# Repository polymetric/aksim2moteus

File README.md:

# aksim2moteus

RS422 adapter with a pinout specifically to adapt a moteus to an aksim2 

screw pattern is M2 - 10.2 x 12.7 mm

overall board dimensions 25.4 x 17.8 mm

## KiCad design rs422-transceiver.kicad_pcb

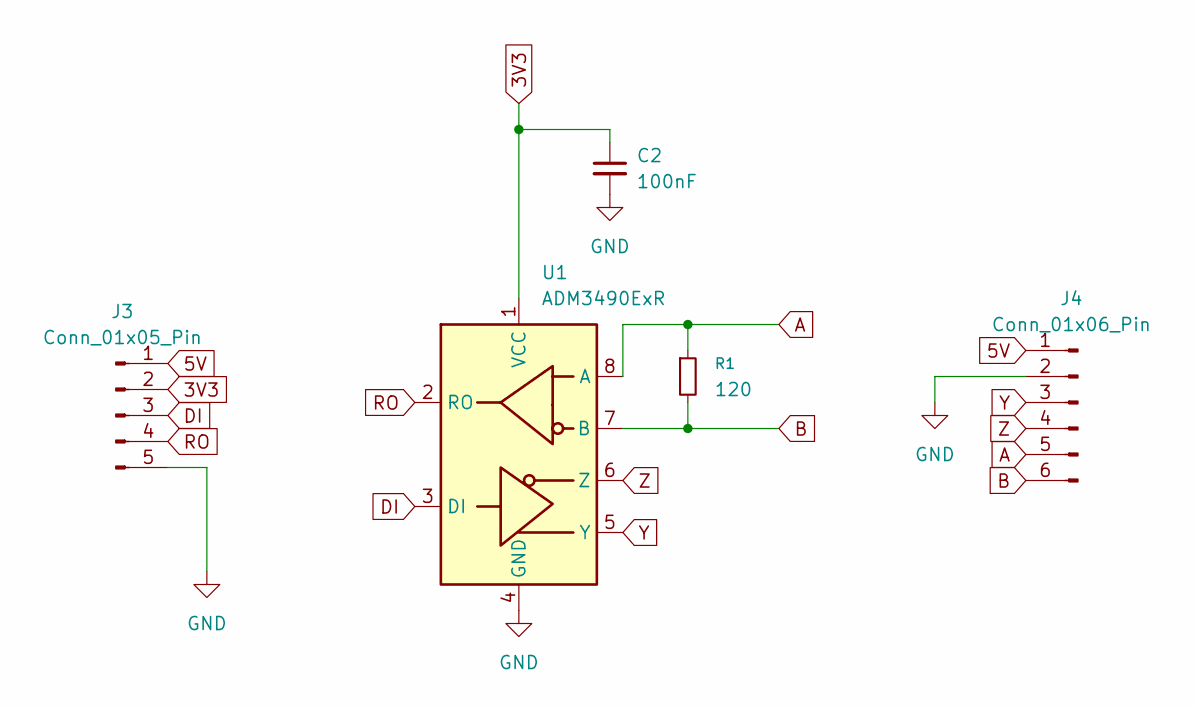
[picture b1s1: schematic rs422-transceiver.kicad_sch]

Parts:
C2: 100nF; C_0603_1608Metric
J3: Conn_01x05_Pin; PinHeader_1x05_P2.54mm_Vertical
J4: Conn_01x06_Pin; PinHeader_1x06_P2.54mm_Vertical
R1: 120; R_0603_1608Metric
U1: ADM3490ExR; SOIC-8_3.9x4.9mm_P1.27mm

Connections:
3V3: C2.1, J3.2, U1.1 (VCC)
5V: J3.1, J4.1
A: J4.5, R1.1, U1.8 (A)
B: J4.6, R1.2, U1.7 (B)
DI: J3.3, U1.3 (DI)
GND: C2.2, J3.5, J4.2, U1.4 (GND)
RO: J3.4, U1.2 (RO)
Y: J4.3, U1.5 (Y)
Z: J4.4, U1.6 (Z)

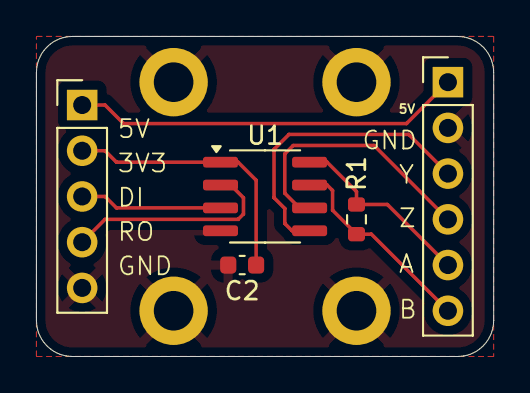
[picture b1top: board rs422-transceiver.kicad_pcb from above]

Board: 2 copper layers, 25.4 x 17.8 mm, 5 parts (0 on the bottom side), 9 nets.

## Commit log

2025-08-05 C2 -> C1

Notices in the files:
rs422-transceiver.kicad_pcb:
copyright (c) 2025 Eli Rutan
